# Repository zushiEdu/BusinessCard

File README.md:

# Business Card

This is my business card.

My business card is a PCB, using the STM32F103C8T6 microcontroller as it's brain.

The STM32 is connected to 6 push buttons and a 12x12 LED matrix. The push buttons and LED matrix are laid out to look like a GameBoy Classic. 

The business card has a collection of common engineering related symbols, values, equations, and footprints on the back.

The STM32 is programmed to simulate John Conway's Game of Life. The push buttons allow you to control the game board and the power of the system.

To toggle edit mode, the user can press A. While the game is not in edit mode, pressing B turns on and off the screen.

The Up/Down/Left/Right buttons move the cursor around when in edit mode. While in edit mode, the cursor will flash and the user can press B to toggle the hovered pixel.

Some cool patterns are printed across the front of the PCB, these are patterns that do cool things in Conway's Game of Life.

The QR code to my portfolio, and some contact info is also on the front of the PCB.

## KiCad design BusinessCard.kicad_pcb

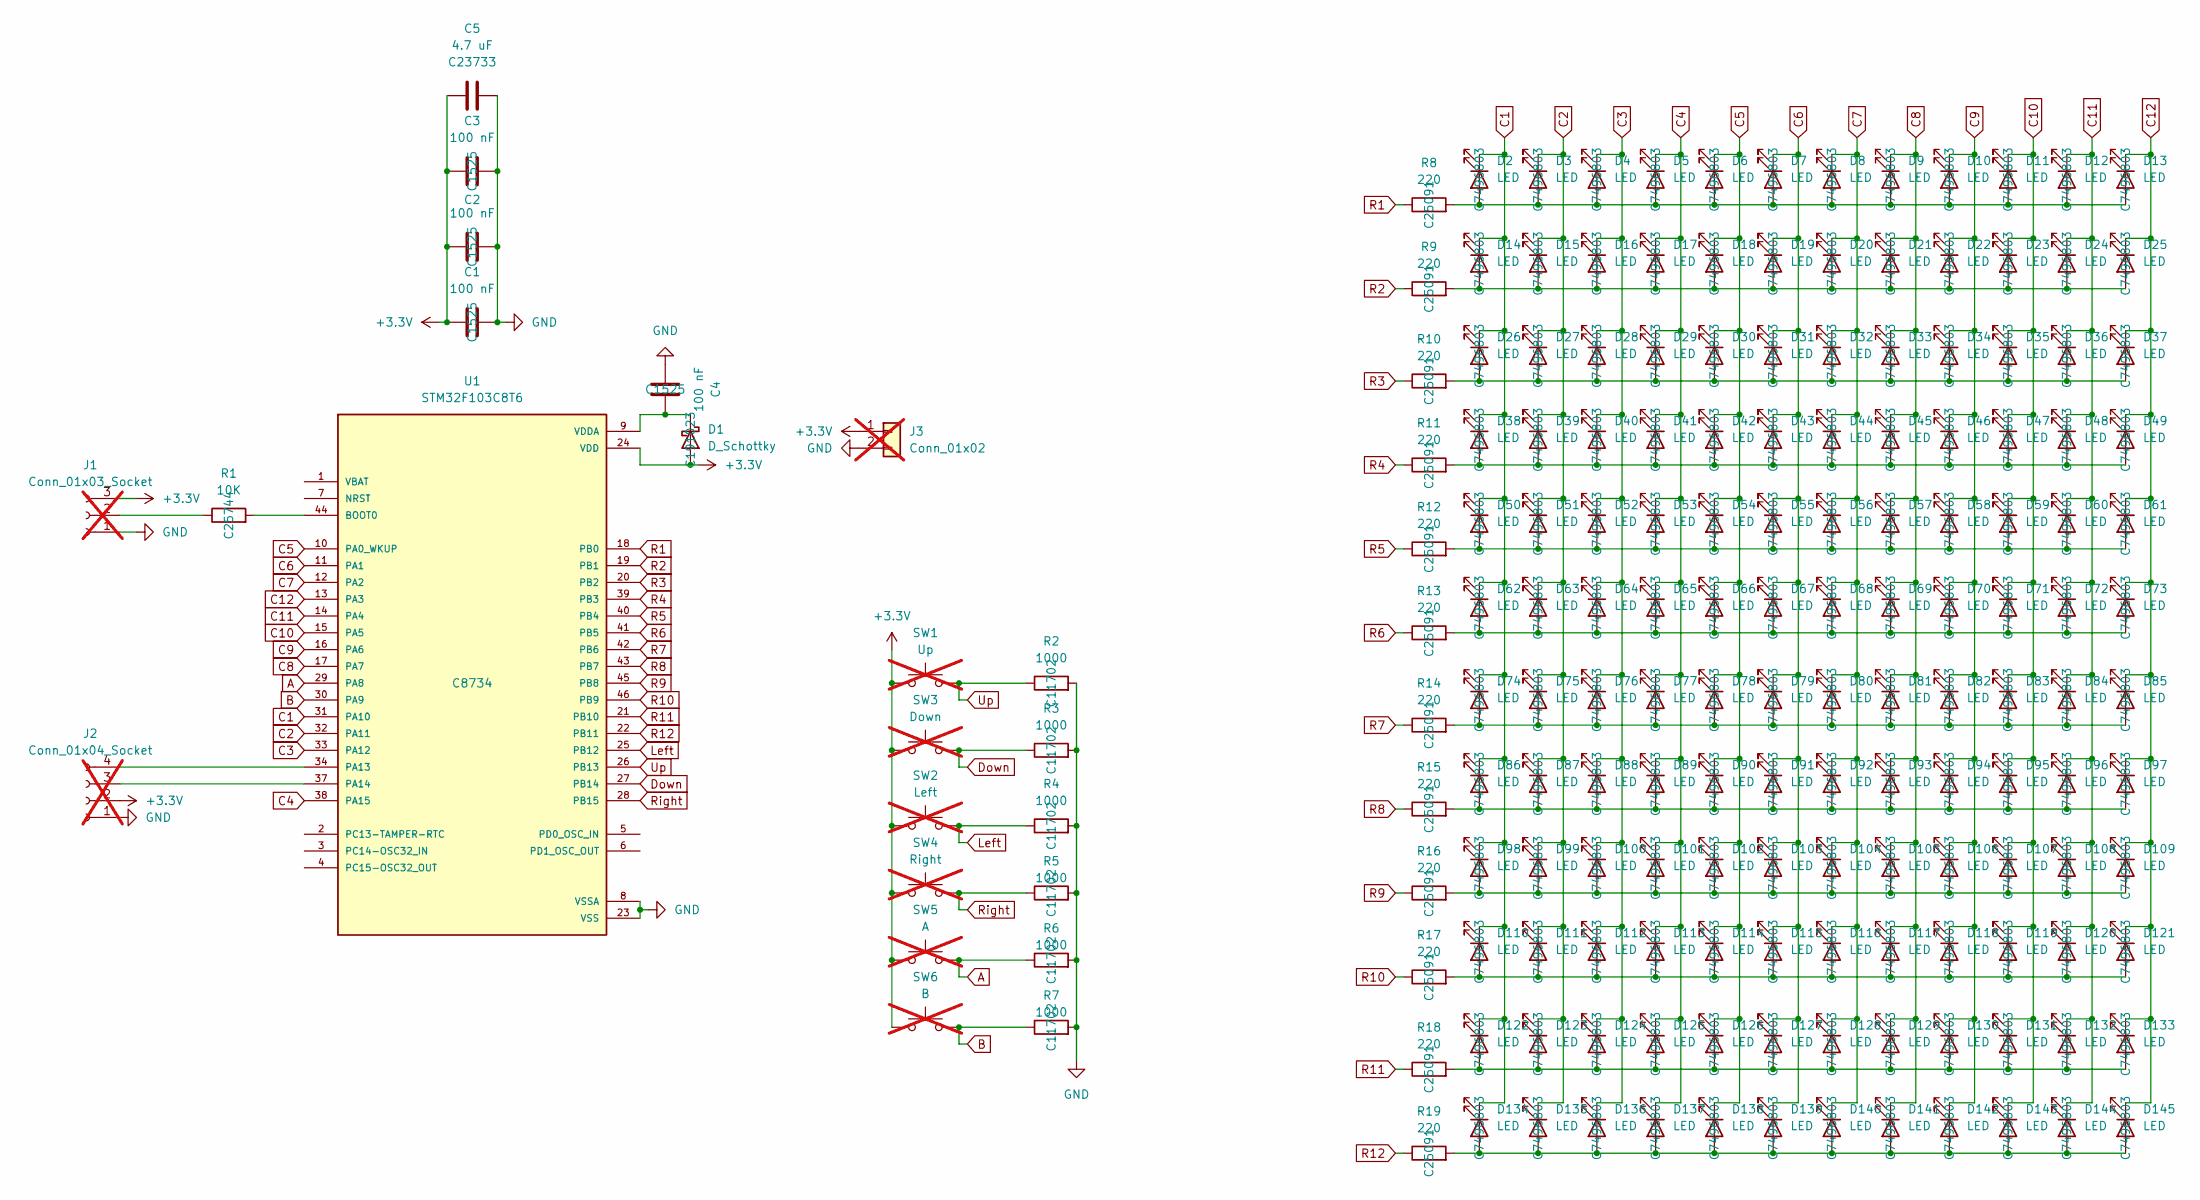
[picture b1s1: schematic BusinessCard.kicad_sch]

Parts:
C1, C2, C3, C4: 100 nF; C_0402_1005Metric_Pad0.74x0.62mm_HandSolder; LCSC C1525
C5: 4.7 uF; C_0402_1005Metric_Pad0.74x0.62mm_HandSolder; LCSC C23733
D1: D_Schottky; D_SOD-323; LCSC C191023
D2, D3, D4, D5, D6, D7, D8, D9, D10, D11, D12, D13, D14, D15, D16, D17, D18, D19, D20, D21, D22, D23, D24, D25, D26, D27, D28, D29, D30, D31, D32, D33, D34, D35, D36, D37, D38, D39, D40, D41, D42, D43, D44, D45, D46, D47, D48, D49, D50, D51, D52, D53, D54, D55, D56, D57, D58, D59, D60, D61, D62, D63, D64, D65, D66, D67, D68, D69, D70, D71, D72, D73, D74, D75, D76, D77, D78, D79, D80, D81, D82, D83, D84, D85, D86, D87, D88, D89, D90, D91, D92, D93, D94, D95, D96, D97, D98, D99, D100, D101, D102, D103, D104, D105, D106, D107, D108, D109, D110, D111, D112, D113, D114, D115, D116, D117, D118, D119, D120, D121, D122, D123, D124, D125, D126, D127, D128, D129, D130, D131, D132, D133, D134, D135, D136, D137, D138, D139, D140, D141, D142, D143, D144, D145: LED; LED_0603_1608Metric_Notext; LCSC C7496803
J1: Conn_01x03_Socket; RoundSolderPad_1x3_1mm; not fitted
J2: Conn_01x04_Socket; RoundSolderPad_1x4_1mm; not fitted
J3: Conn_01x02; Keystone_1057; not fitted
R1: 10K; R_0402_1005Metric_Pad0.72x0.64mm_HandSolder_Notext; LCSC C25744
R2, R3, R4, R5, R6, R7: 1000; R_0402_1005Metric_Pad0.72x0.64mm_HandSolder_Notext; LCSC C11702
R8, R9, R10, R11, R12, R13, R14, R15, R16, R17, R18, R19: 220; R_0402_1005Metric_Pad0.72x0.64mm_HandSolder_Notext; LCSC C25091
SW1: Up; SW_TL1015AF160QG; not fitted
SW2: Left; SW_TL1015AF160QG; not fitted
SW3: Down; SW_TL1015AF160QG; not fitted
SW4: Right; SW_TL1015AF160QG; not fitted
SW5: A; SW_TL1015AF160QG; not fitted
SW6: B; SW_TL1015AF160QG; not fitted
U1: STM32F103C8T6; QFP50P900X900X160-48N; PARTREV 10; LCSC C8734

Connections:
+3.3V: C1.1, C2.1, C3.1, C5.1, D1.2 (A), J1.3, J2.2, J3.1, SW1.1, SW2.1, SW3.1, SW4.1, SW5.1, SW6.1, U1.24 (VDD), U1.36 (VDD), U1.48 (VDD)
A: R6.1, SW5.2, U1.29 (PA8)
B: R7.1, SW6.2, U1.30 (PA9)
C1: D2.1 (K), D14.1 (K), D26.1 (K), D38.1 (K), D50.1 (K), D62.1 (K), D74.1 (K), D86.1 (K), D98.1 (K), D110.1 (K), D122.1 (K), D134.1 (K), U1.31 (PA10)
C2: D3.1 (K), D15.1 (K), D27.1 (K), D39.1 (K), D51.1 (K), D63.1 (K), D75.1 (K), D87.1 (K), D99.1 (K), D111.1 (K), D123.1 (K), D135.1 (K), U1.32 (PA11)
C3: D4.1 (K), D16.1 (K), D28.1 (K), D40.1 (K), D52.1 (K), D64.1 (K), D76.1 (K), D88.1 (K), D100.1 (K), D112.1 (K), D124.1 (K), D136.1 (K), U1.33 (PA12)
C4: D5.1 (K), D17.1 (K), D29.1 (K), D41.1 (K), D53.1 (K), D65.1 (K), D77.1 (K), D89.1 (K), D101.1 (K), D113.1 (K), D125.1 (K), D137.1 (K), U1.38 (PA15)
C5: D6.1 (K), D18.1 (K), D30.1 (K), D42.1 (K), D54.1 (K), D66.1 (K), D78.1 (K), D90.1 (K), D102.1 (K), D114.1 (K), D126.1 (K), D138.1 (K), U1.10 (PA0_WKUP)
C6: D7.1 (K), D19.1 (K), D31.1 (K), D43.1 (K), D55.1 (K), D67.1 (K), D79.1 (K), D91.1 (K), D103.1 (K), D115.1 (K), D127.1 (K), D139.1 (K), U1.11 (PA1)
C7: D8.1 (K), D20.1 (K), D32.1 (K), D44.1 (K), D56.1 (K), D68.1 (K), D80.1 (K), D92.1 (K), D104.1 (K), D116.1 (K), D128.1 (K), D140.1 (K), U1.12 (PA2)
C8: D9.1 (K), D21.1 (K), D33.1 (K), D45.1 (K), D57.1 (K), D69.1 (K), D81.1 (K), D93.1 (K), D105.1 (K), D117.1 (K), D129.1 (K), D141.1 (K), U1.17 (PA7)
C9: D10.1 (K), D22.1 (K), D34.1 (K), D46.1 (K), D58.1 (K), D70.1 (K), D82.1 (K), D94.1 (K), D106.1 (K), D118.1 (K), D130.1 (K), D142.1 (K), U1.16 (PA6)
C10: D11.1 (K), D23.1 (K), D35.1 (K), D47.1 (K), D59.1 (K), D71.1 (K), D83.1 (K), D95.1 (K), D107.1 (K), D119.1 (K), D131.1 (K), D143.1 (K), U1.15 (PA5)
C11: D12.1 (K), D24.1 (K), D36.1 (K), D48.1 (K), D60.1 (K), D72.1 (K), D84.1 (K), D96.1 (K), D108.1 (K), D120.1 (K), D132.1 (K), D144.1 (K), U1.14 (PA4)
C12: D13.1 (K), D25.1 (K), D37.1 (K), D49.1 (K), D61.1 (K), D73.1 (K), D85.1 (K), D97.1 (K), D109.1 (K), D121.1 (K), D133.1 (K), D145.1 (K), U1.13 (PA3)
Down: R3.1, SW3.2, U1.27 (PB14)
GND: C1.2, C2.2, C3.2, C4.1, C5.2, J1.1, J2.1, J3.2, R2.2, R3.2, R4.2, R5.2, R6.2, R7.2, U1.8 (VSSA), U1.23 (VSS), U1.35 (VSS), U1.47 (VSS)
Left: R4.1, SW2.2, U1.25 (PB12)
unnamed: C4.2, D1.1 (K), U1.9 (VDDA)
unnamed: D2.2 (A), D3.2 (A), D4.2 (A), D5.2 (A), D6.2 (A), D7.2 (A), D8.2 (A), D9.2 (A), D10.2 (A), D11.2 (A), D12.2 (A), D13.2 (A), R8.2
unnamed: D14.2 (A), D15.2 (A), D16.2 (A), D17.2 (A), D18.2 (A), D19.2 (A), D20.2 (A), D21.2 (A), D22.2 (A), D23.2 (A), D24.2 (A), D25.2 (A), R9.2
unnamed: D26.2 (A), D27.2 (A), D28.2 (A), D29.2 (A), D30.2 (A), D31.2 (A), D32.2 (A), D33.2 (A), D34.2 (A), D35.2 (A), D36.2 (A), D37.2 (A), R10.2
unnamed: D38.2 (A), D39.2 (A), D40.2 (A), D41.2 (A), D42.2 (A), D43.2 (A), D44.2 (A), D45.2 (A), D46.2 (A), D47.2 (A), D48.2 (A), D49.2 (A), R11.2
unnamed: D50.2 (A), D51.2 (A), D52.2 (A), D53.2 (A), D54.2 (A), D55.2 (A), D56.2 (A), D57.2 (A), D58.2 (A), D59.2 (A), D60.2 (A), D61.2 (A), R12.2
unnamed: D62.2 (A), D63.2 (A), D64.2 (A), D65.2 (A), D66.2 (A), D67.2 (A), D68.2 (A), D69.2 (A), D70.2 (A), D71.2 (A), D72.2 (A), D73.2 (A), R13.2
unnamed: D74.2 (A), D75.2 (A), D76.2 (A), D77.2 (A), D78.2 (A), D79.2 (A), D80.2 (A), D81.2 (A), D82.2 (A), D83.2 (A), D84.2 (A), D85.2 (A), R14.2
unnamed: D86.2 (A), D87.2 (A), D88.2 (A), D89.2 (A), D90.2 (A), D91.2 (A), D92.2 (A), D93.2 (A), D94.2 (A), D95.2 (A), D96.2 (A), D97.2 (A), R15.2
unnamed: D98.2 (A), D99.2 (A), D100.2 (A), D101.2 (A), D102.2 (A), D103.2 (A), D104.2 (A), D105.2 (A), D106.2 (A), D107.2 (A), D108.2 (A), D109.2 (A), R16.2
unnamed: D110.2 (A), D111.2 (A), D112.2 (A), D113.2 (A), D114.2 (A), D115.2 (A), D116.2 (A), D117.2 (A), D118.2 (A), D119.2 (A), D120.2 (A), D121.2 (A), R17.2
unnamed: D122.2 (A), D123.2 (A), D124.2 (A), D125.2 (A), D126.2 (A), D127.2 (A), D128.2 (A), D129.2 (A), D130.2 (A), D131.2 (A), D132.2 (A), D133.2 (A), R18.2
unnamed: D134.2 (A), D135.2 (A), D136.2 (A), D137.2 (A), D138.2 (A), D139.2 (A), D140.2 (A), D141.2 (A), D142.2 (A), D143.2 (A), D144.2 (A), D145.2 (A), R19.2
unnamed: J1.2, R1.1
unnamed: J2.3, U1.37 (PA14)
unnamed: J2.4, U1.34 (PA13)
unnamed: R1.2, U1.44 (BOOT0)
R1: R8.1, U1.18 (PB0)
R2: R9.1, U1.19 (PB1)
R3: R10.1, U1.20 (PB2)
R4: R11.1, U1.39 (PB3)
R5: R12.1, U1.40 (PB4)
R6: R13.1, U1.41 (PB5)
R7: R14.1, U1.42 (PB6)
R8: R15.1, U1.43 (PB7)
R9: R16.1, U1.45 (PB8)
R10: R17.1, U1.46 (PB9)
R11: R18.1, U1.21 (PB10)
R12: R19.1, U1.22 (PB11)
Right: R5.1, SW4.2, U1.28 (PB15)
Up: R2.1, SW1.2, U1.26 (PB13)

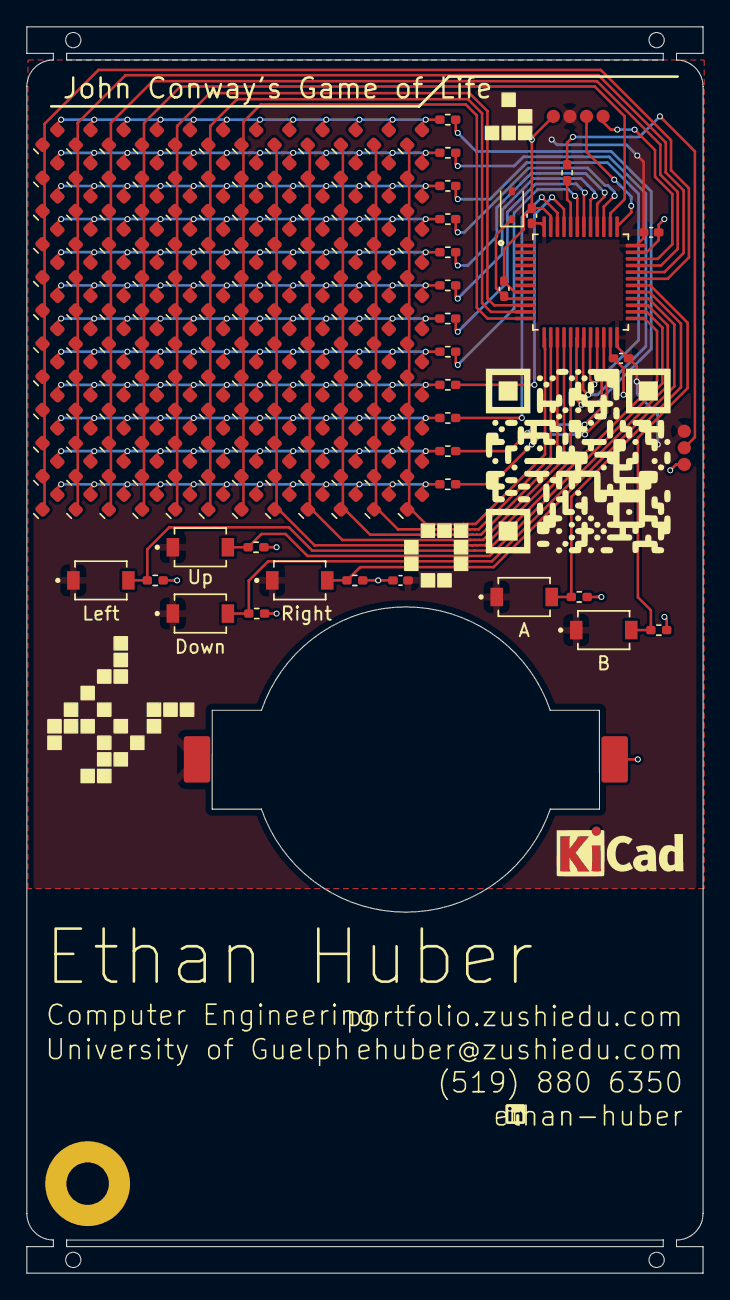
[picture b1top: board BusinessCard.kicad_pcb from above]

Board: 2 copper layers, 51.0 x 94.0 mm, 179 parts (0 on the bottom side), 49 nets.

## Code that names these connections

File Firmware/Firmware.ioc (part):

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Mcu.Name=STM32F103C(8-B)Tx
Mcu.Package=LQFP48
Mcu.UserName=STM32F103C8Tx
PA0-WKUP.Signal=GPIO_Output
PA1.Signal=GPIO_Output
PA10.Signal=GPIO_Output
PA11.Signal=GPIO_Output
PA12.Signal=GPIO_Output
PA13.Mode=Serial_Wire
PA13.Signal=SYS_JTMS-SWDIO
PA14.Mode=Serial_Wire
PA14.Signal=SYS_JTCK-SWCLK
PA15.Signal=GPIO_Output
PA2.Signal=GPIO_Output
PA3.Signal=GPIO_Output
PA4.Signal=GPIO_Output
PA5.Signal=GPIO_Output
PA6.Signal=GPIO_Output
PA7.Signal=GPIO_Output
PA8.Signal=GPIO_Input
PA9.Signal=GPIO_Input
PB0.Signal=GPIO_Output
PB1.Signal=GPIO_Output
PB10.Signal=GPIO_Output
PB11.Signal=GPIO_Output
PB12.Signal=GPIO_Input
PB13.Signal=GPIO_Input
PB14.Signal=GPIO_Input
PB15.Signal=GPIO_Input
PB2.Signal=GPIO_Output
PB3.Signal=GPIO_Output
PB4.Signal=GPIO_Output
PB5.Signal=GPIO_Output
PB6.Signal=GPIO_Output
PB7.Signal=GPIO_Output
PB8.Signal=GPIO_Output
PB9.Signal=GPIO_Output
board=custom

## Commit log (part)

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2025-12-16 First Sync
2025-12-16 Add various SMD resistor footprints and mounting hole
    Added new SMD resistor footprints (0201, 0402, 0805, 2010, 2512) and a 3.2mm M3 mounting hole to the PCB layout. Updated backup files and removed an old autosave.
2025-12-19 Add logo footprint and update TQFP-32 package
    Added a new 'LOGO' footprint to the front copper layer and replaced the 'R_0201_0603Metric' resistor footprint with a 'TQFP-32_7x7mm_P0.8mm' package on the back copper layer. Updated backup files and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
2025-12-20 Rearranged back and added KiCad logo
    - Rearranged back to avoid via collision
    - Added KiCad logo
    - Moved some via's for cleanliness
    - Moved keychain hole label position
2025-12-22 Fabrication edits
    - Added JLCPCB component part numbers
2025-12-23 Switched LED footprint and fixed row traces
    - Switched LED footprints from 0402 to 0603 to reduce assembly cost
    - Added back row traces that were accidentally removed in an earlier commit
2025-12-24 Changed model of buttons to cheaper version
2026-01-11 Static oscillator Conway's Game of Life Firmware
2026-01-11 Add project details for business card PCB
    Added detailed description of the business card project, including its features and functionality.
2026-01-11 Added board editing
2026-01-19 Update README with clearer game control instructions
    Clarified instructions for edit mode and game controls.
